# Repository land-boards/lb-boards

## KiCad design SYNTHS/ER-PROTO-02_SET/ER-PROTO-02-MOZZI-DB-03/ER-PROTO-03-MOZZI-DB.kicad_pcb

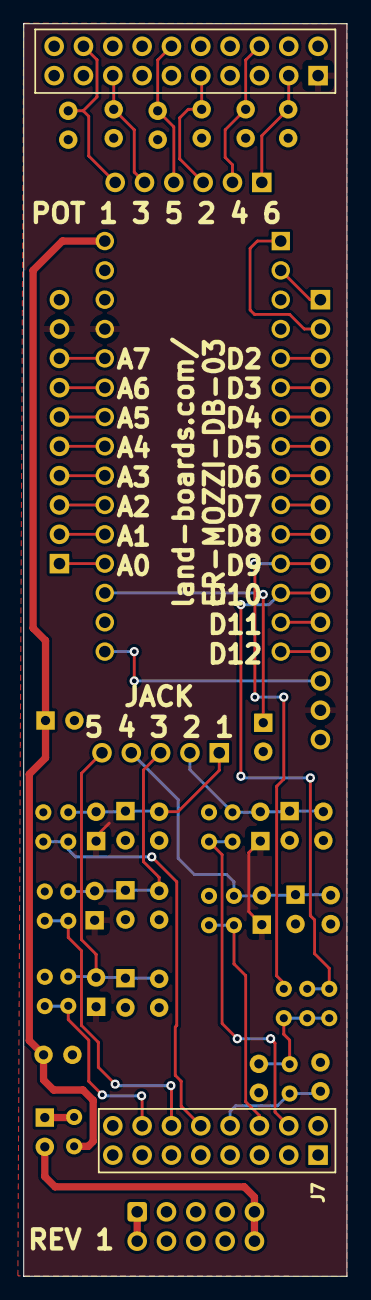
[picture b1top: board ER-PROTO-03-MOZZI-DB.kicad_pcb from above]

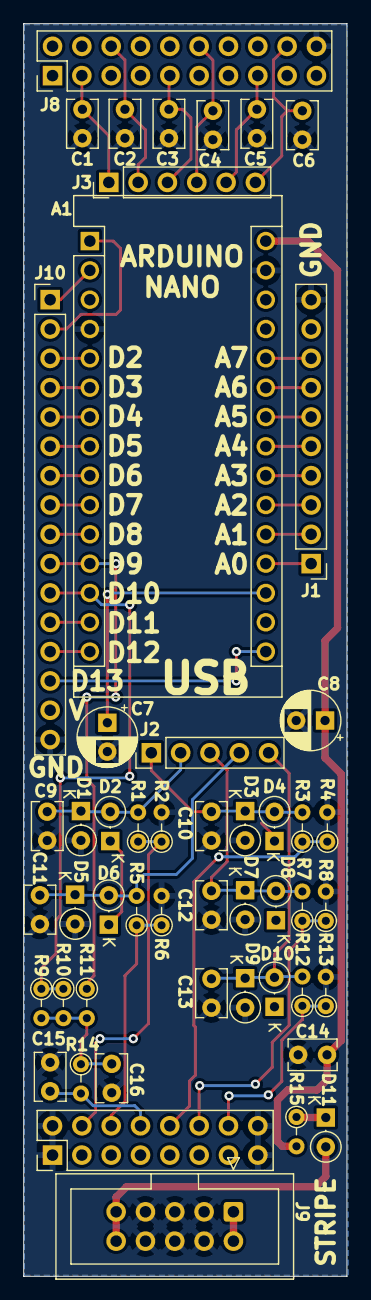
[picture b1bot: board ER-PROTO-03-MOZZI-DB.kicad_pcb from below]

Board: 2 copper layers, 28.0 x 108.5 mm, 50 parts (50 on the bottom side), 47 nets.

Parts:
A1: Arduino_Nano_v3.x; Arduino_Nano
C1, C2, C3, C4, C5, C6, C9, C10, C11, C12, C13, C14: 0.1uF; C_Rect_L4.0mm_W2.5mm_P2.50mm
C7: 10uF; CP_Radial_D5.0mm_P2.50mm
C8: 47uF; CP_Radial_D5.0mm_P2.50mm
C15: 10nF; C_Rect_L4.0mm_W2.5mm_P2.50mm
C16: 4.7nF; C_Rect_L4.0mm_W2.5mm_P2.50mm
D1, D2, D3, D4, D5, D6, D7, D8, D9, D10, D11: BAT41; D_DO-35_SOD27_P2.54mm_Vertical_KathodeUp
J1: Conn_01x10; PinHeader_1x10_P2.54mm_Vertical
J2: Conn_01x05; PinHeader_1x05_P2.54mm_Vertical
J3: Conn_01x06; PinHeader_1x06_P2.54mm_Vertical
J7: PROTO02_JACKS; PinHeader_2x08_P2.54mm_Vertical
J8: PROTO02_POTS; PinHeader_2x10_P2.54mm_Vertical
J9: CONN, IDC, 2X5; IDC-Header_2x05_P2.54mm_Vertical
J10: Conn_01x16; PinHeader_1x16_P2.54mm_Vertical
R1, R3, R5, R7, R12: 10K; R_Axial_DIN0204_L3.6mm_D1.6mm_P2.54mm_Vertical
R2, R4, R6, R8, R13: 100K; R_Axial_DIN0204_L3.6mm_D1.6mm_P2.54mm_Vertical
R9, R10: 1M; R_Axial_DIN0204_L3.6mm_D1.6mm_P2.54mm_Vertical
R11, R14: 3.9K; R_Axial_DIN0204_L3.6mm_D1.6mm_P2.54mm_Vertical
R15: 10; R_Axial_DIN0204_L3.6mm_D1.6mm_P2.54mm_Vertical

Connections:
+5V: A1.27 (+5V), D2.1 (K), D4.1 (K), D6.1 (K), D8.1 (K), D10.1 (K), J1.9, J8.1 (VCC), J10.15
+12P: A1.30 (VIN), C8.1, C14.1, R15.2
+12V: D11.2 (A), J9.9, J9.10
-12V: J9.1, J9.2
/ANA0: A1.19 (A0), J1.1
/ANA1: A1.20 (A1), J1.2
/ANA2: A1.21 (A2), J1.3
/ANA3: A1.22 (A3), J1.4
/ANA4: A1.23 (A4), J1.5
/ANA5: A1.24 (A5), J1.6
/ANA6: A1.25 (A6), J1.7
/ANA7: A1.26 (A7), J1.8
/D0_RX: A1.2 (D0/RX), J10.1
/D1_TX: A1.1 (D1/TX), J10.2
/D2: A1.5 (D2), J10.3
/D3: A1.6 (D3), J10.4
/D4: A1.7 (D4), J10.5
/D5: A1.8 (D5), J10.6
/D6: A1.9 (D6), J10.7
/D7: A1.10 (D7), J10.8
/D8: A1.11 (D8), J10.9
/D9: A1.12 (D9), J10.10, R11.1
/D10: A1.13 (D10), J10.11, R9.1, R10.1
/D11: A1.14 (D11), J10.12
/D12: A1.15 (D12), J10.13
/D13: A1.16 (D13), J10.14
/J1-T: J7.10 (J1_T), R3.1, R4.1
/J1-TIP: C10.1, D3.1 (K), D4.2 (A), J2.1, R3.2
/J2-T: J7.4 (J2_T), R1.1, R2.1
/J2-TIP: C9.1, D1.1 (K), D2.2 (A), J2.2, R1.2
/J3-T: J7.12 (J3_T), R7.1, R8.1
/J3-TIP: C12.1, D7.1 (K), D8.2 (A), J2.3, R7.2
/J4-T: J7.6 (J4_T), R5.1, R6.1
/J4-TIP: C11.1, D5.1 (K), D6.2 (A), J2.4, R5.2
/J5-T: J7.14 (J5_T), R12.1, R13.1
/J5-TIP: C13.1, D9.1 (K), D10.2 (A), J2.5, R12.2
/J6-T: C15.1, J7.8 (J6_T), R14.2
/POT1-2: C6.1, J3.6, J8.18 (POT1_2_W)
/POT2-2: C3.1, J3.3, J8.9 (POT2_2_W)
/POT3-2: C5.1, J3.5, J8.15 (POT3_2_W)
/POT4-2: C2.1, J3.2, J8.6 (POT4_2_W)
/POT5-2: C4.1, J3.4, J8.12 (POT5_2_W)
/POT6-2: C1.1, J3.1, J8.3 (POT6_2_W)
GND: A1.4 (GND), A1.29 (GND), C1.2, C2.2, C3.2, C4.2, C5.2, C6.2, C7.2, C8.2, C9.2, C10.2, C11.2, C12.2, C13.2, C14.2, C15.2, C16.2, D1.2 (A), D3.2 (A), D5.2 (A), D7.2 (A), D9.2 (A), J1.10, J7.1 (GND), J7.2 (GND), J7.15 (GND), J7.16 (GND), J8.20 (GND), J9.3, J9.4, J9.5, J9.6, J9.7, J9.8, J10.16, R2.2, R4.2, R6.2, R8.2, R13.2
unnamed: A1.18 (AREF), C7.1
unnamed: C16.1, R9.2, R10.2, R11.2, R14.1
unnamed: D11.1 (K), R15.1

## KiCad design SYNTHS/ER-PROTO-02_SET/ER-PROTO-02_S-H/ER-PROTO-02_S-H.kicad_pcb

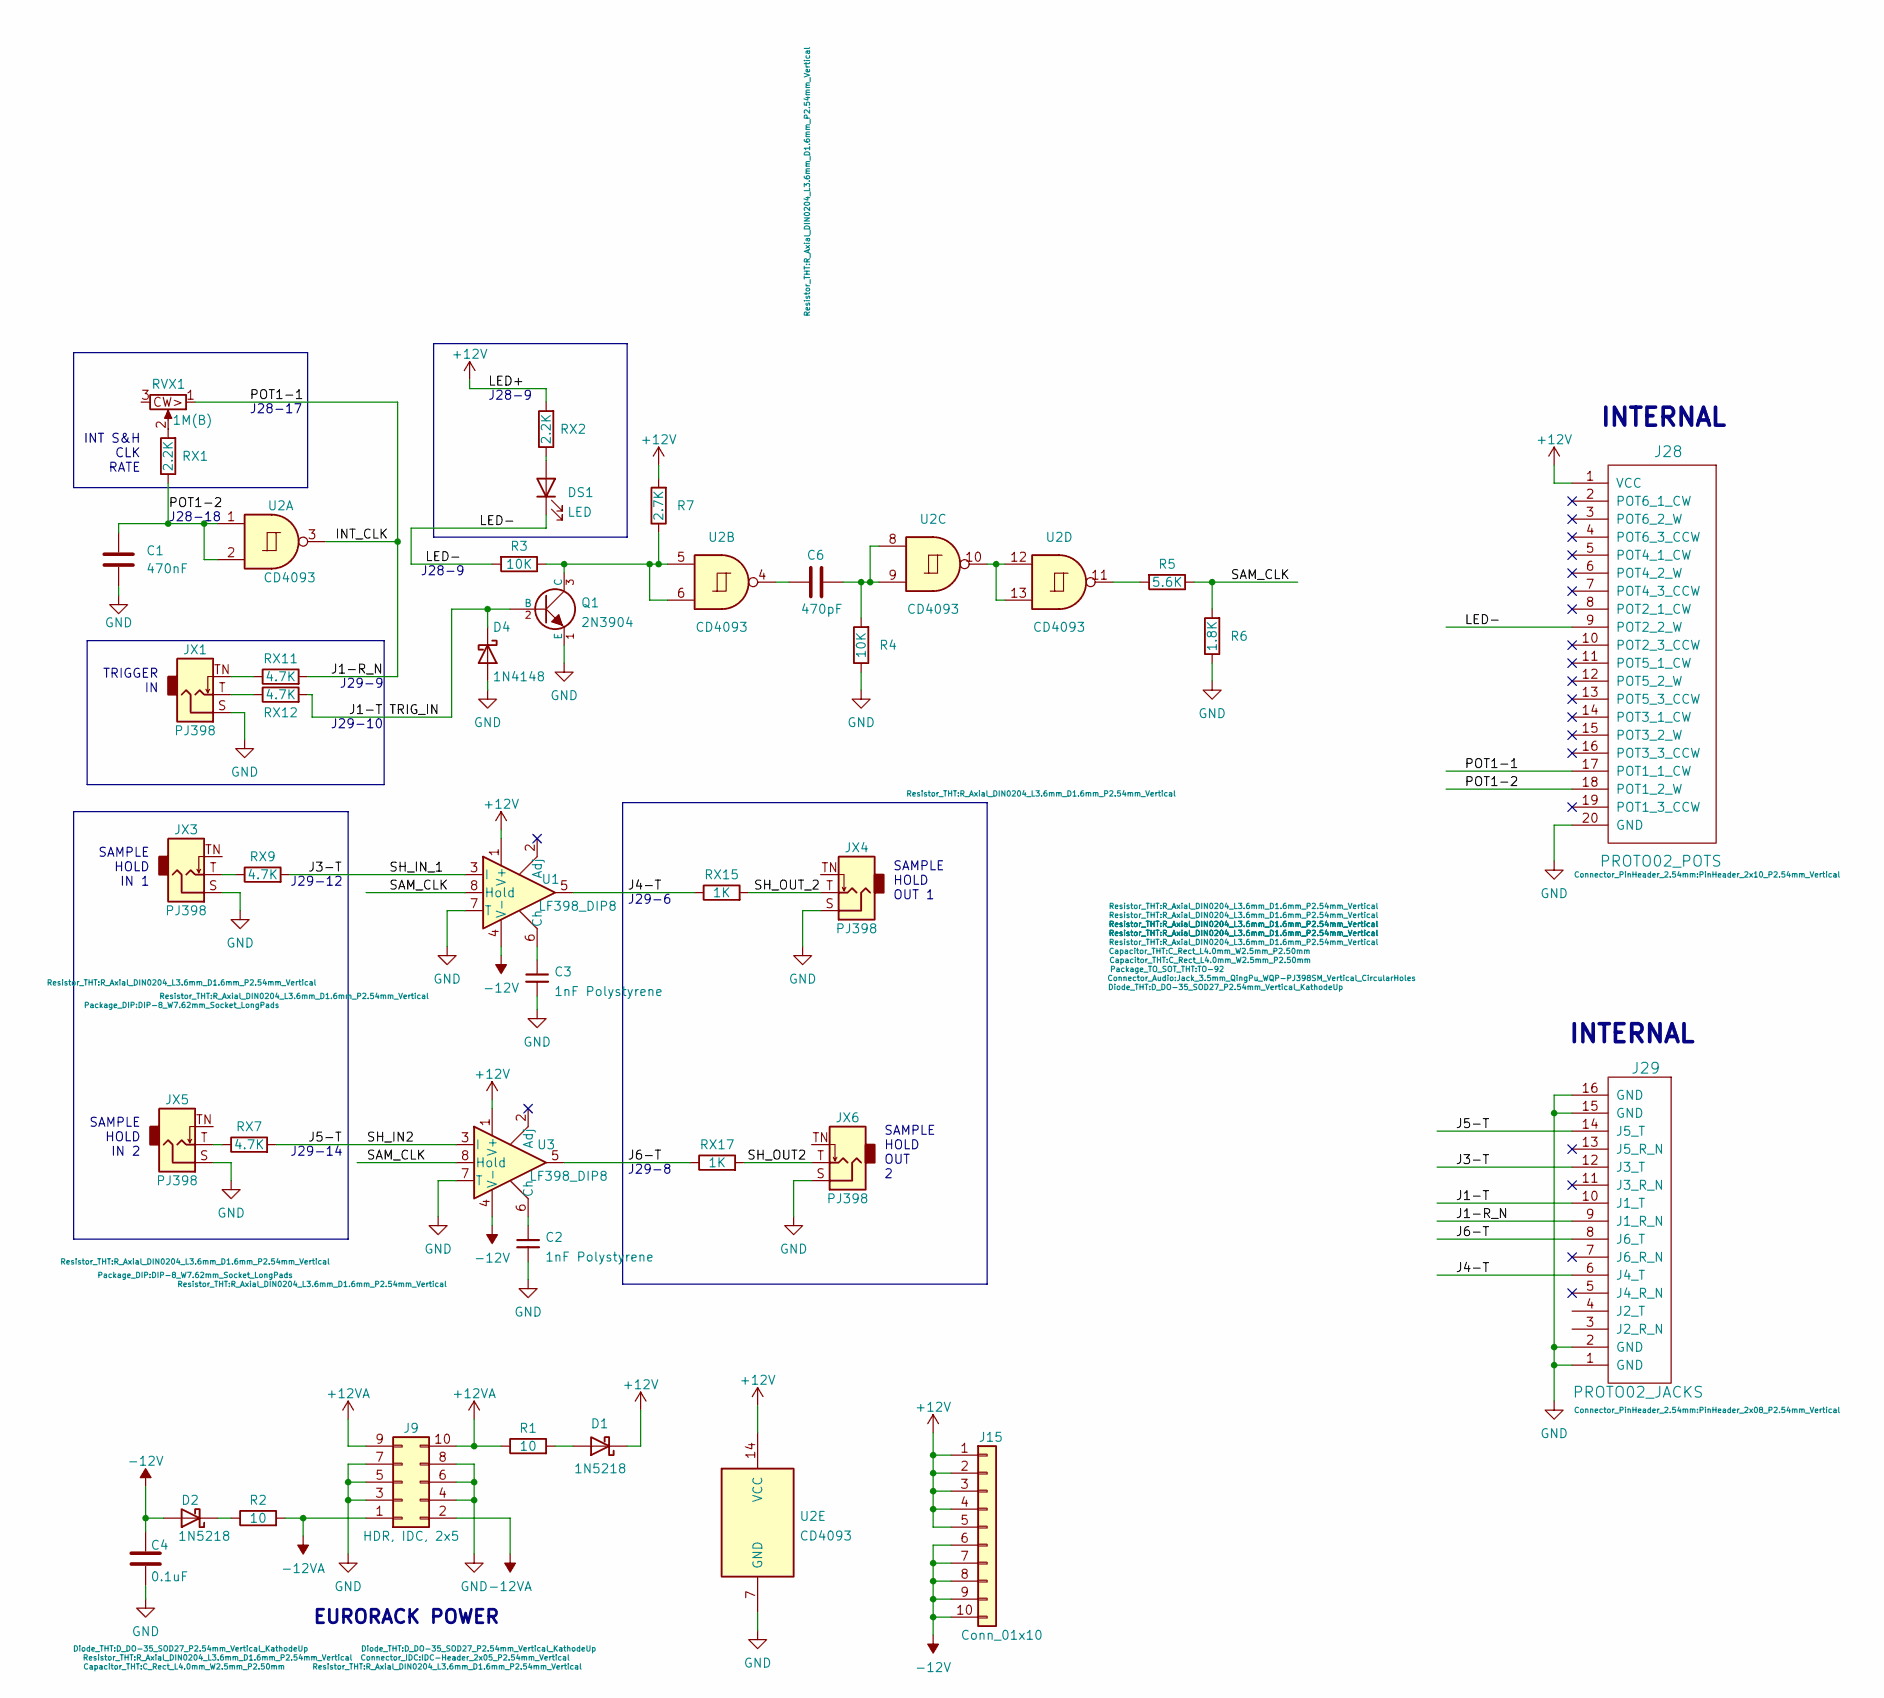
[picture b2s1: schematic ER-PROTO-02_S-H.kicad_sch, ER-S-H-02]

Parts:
C1: 470nF; C_Rect_L4.0mm_W2.5mm_P2.50mm
C2, C3: 1nF Polystyrene; C_Radial_D5.0mm_H7.0mm_P2.00mm
C4: 0.1uF; C_Rect_L4.0mm_W2.5mm_P2.50mm
C6: 470pF; C_Rect_L4.0mm_W2.5mm_P2.50mm
D1, D2: 1N5218; D_DO-35_SOD27_P2.54mm_Vertical_KathodeUp
D4: 1N4148; D_DO-35_SOD27_P2.54mm_Vertical_KathodeUp
DS1: LED; LED_D5.0mm
J9: HDR, IDC, 2x5; IDC-Header_2x05_P2.54mm_Vertical
J15: Conn_01x10; PinHeader_1x10_P2.54mm_Vertical
J28: PROTO02_POTS; PinHeader_2x10_P2.54mm_Vertical
J29: PROTO02_JACKS; PinHeader_2x08_P2.54mm_Vertical
JX1, JX3, JX4, JX5, JX6: PJ398; Jack_3.5mm_QingPu_WQP-PJ398SM_Vertical_CircularHoles
Q1: 2N3904; TO-92
R1, R2: 10; R_Axial_DIN0204_L3.6mm_D1.6mm_P2.54mm_Vertical
R3, R4: 10K; R_Axial_DIN0204_L3.6mm_D1.6mm_P2.54mm_Vertical
R5: 5.6K; R_Axial_DIN0204_L3.6mm_D1.6mm_P2.54mm_Vertical
R6: 1.8K; R_Axial_DIN0204_L3.6mm_D1.6mm_P2.54mm_Vertical
R7: 2.7K; R_Axial_DIN0204_L3.6mm_D1.6mm_P2.54mm_Vertical
RVX1: 1M(B); RV09ACF
RX1, RX2: 2.2K; R_Axial_DIN0204_L3.6mm_D1.6mm_P2.54mm_Vertical
RX7, RX9, RX11, RX12: 4.7K; R_Axial_DIN0204_L3.6mm_D1.6mm_P2.54mm_Vertical
RX15, RX17: 1K; R_Axial_DIN0204_L3.6mm_D1.6mm_P2.54mm_Vertical
U1, U3: LF398_DIP8; DIP-8_W7.62mm_Socket_LongPads
U2: CD4093; DIP-14_W7.62mm_Socket_LongPads

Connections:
+12V: D1.1 (K), J15.1, J15.2, J15.3, J15.4, J15.5, J28.1 (VCC), R7.2, RX2.2, U1.1 (V+), U2.14 (VCC), U3.1 (V+)
+12VA: J9.9, J9.10, R1.1
-12V: C4.1, D2.2 (A), J15.6, J15.7, J15.8, J15.9, J15.10, U1.4 (V-), U3.4 (V-)
-12VA: J9.1, J9.2, R2.2
/INT_CLK: J28.17 (POT1_1_CW), J29.9 (J1_R_N), RVX1.1, RX11.2, U2.3
/J1-T: D4.1 (K), J29.10 (J1_T), Q1.2 (B), RX12.2
/J3-T: J29.12 (J3_T), RX9.2, U1.3 (I)
/J4-T: J29.6 (J4_T), RX15.1, U1.5
/J5-T: J29.14 (J5_T), RX7.2, U3.3 (I)
/J6-T: J29.8 (J6_T), RX17.1, U3.5
/LED-: DS1.1 (K), J28.9 (POT2_2_W), R3.2
/POT1-2: C1.1, J28.18 (POT1_2_W), RX1.1, U2.1, U2.2
/SAM_CLK: R5.1, R6.2, U1.8 (Hold), U3.8 (Hold)
/SH_OUT2: JX6.T, RX17.2
/SH_OUT_2: JX4.T, RX15.2
GND: C1.2, C2.2, C3.2, C4.2, D4.2 (A), J9.3, J9.4, J9.5, J9.6, J9.7, J9.8, J28.20 (GND), J29.1 (GND), J29.2 (GND), J29.15 (GND), J29.16 (GND), JX1.S, JX3.S, JX4.S, JX5.S, JX6.S, Q1.1 (E), R4.1, R6.1, U1.7 (T), U2.7 (GND), U3.7 (T)
unnamed: C2.1, U3.6 (Ch)
unnamed: C3.1, U1.6 (Ch)
unnamed: C6.1, U2.4
unnamed: C6.2, R4.2, U2.8, U2.9
unnamed: D1.2 (A), R1.2
unnamed: D2.1 (K), R2.1
unnamed: DS1.2 (A), RX2.1
unnamed: JX1.T, RX12.1
unnamed: JX1.TN, RX11.1
unnamed: JX3.T, RX9.1
unnamed: JX5.T, RX7.1
unnamed: Q1.3 (C), R3.1, R7.1, U2.5, U2.6
unnamed: R5.2, U2.11
unnamed: RVX1.2, RX1.2
unnamed: U2.10, U2.12, U2.13

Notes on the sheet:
SAMPLE HOLD OUT 2
EURORACK POWER
INT S&H CLK RATE
J29-8
SAMPLE HOLD OUT 1
J29-14
J28-17
J29-6
SAMPLE HOLD IN 2
J28-9
TRIGGER IN
J28-18
J29-12
SAMPLE HOLD IN 1
J29-9
INTERNAL
J29-10

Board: 2 copper layers, 38 parts (0 on the bottom side), 31 nets, no tracks yet.

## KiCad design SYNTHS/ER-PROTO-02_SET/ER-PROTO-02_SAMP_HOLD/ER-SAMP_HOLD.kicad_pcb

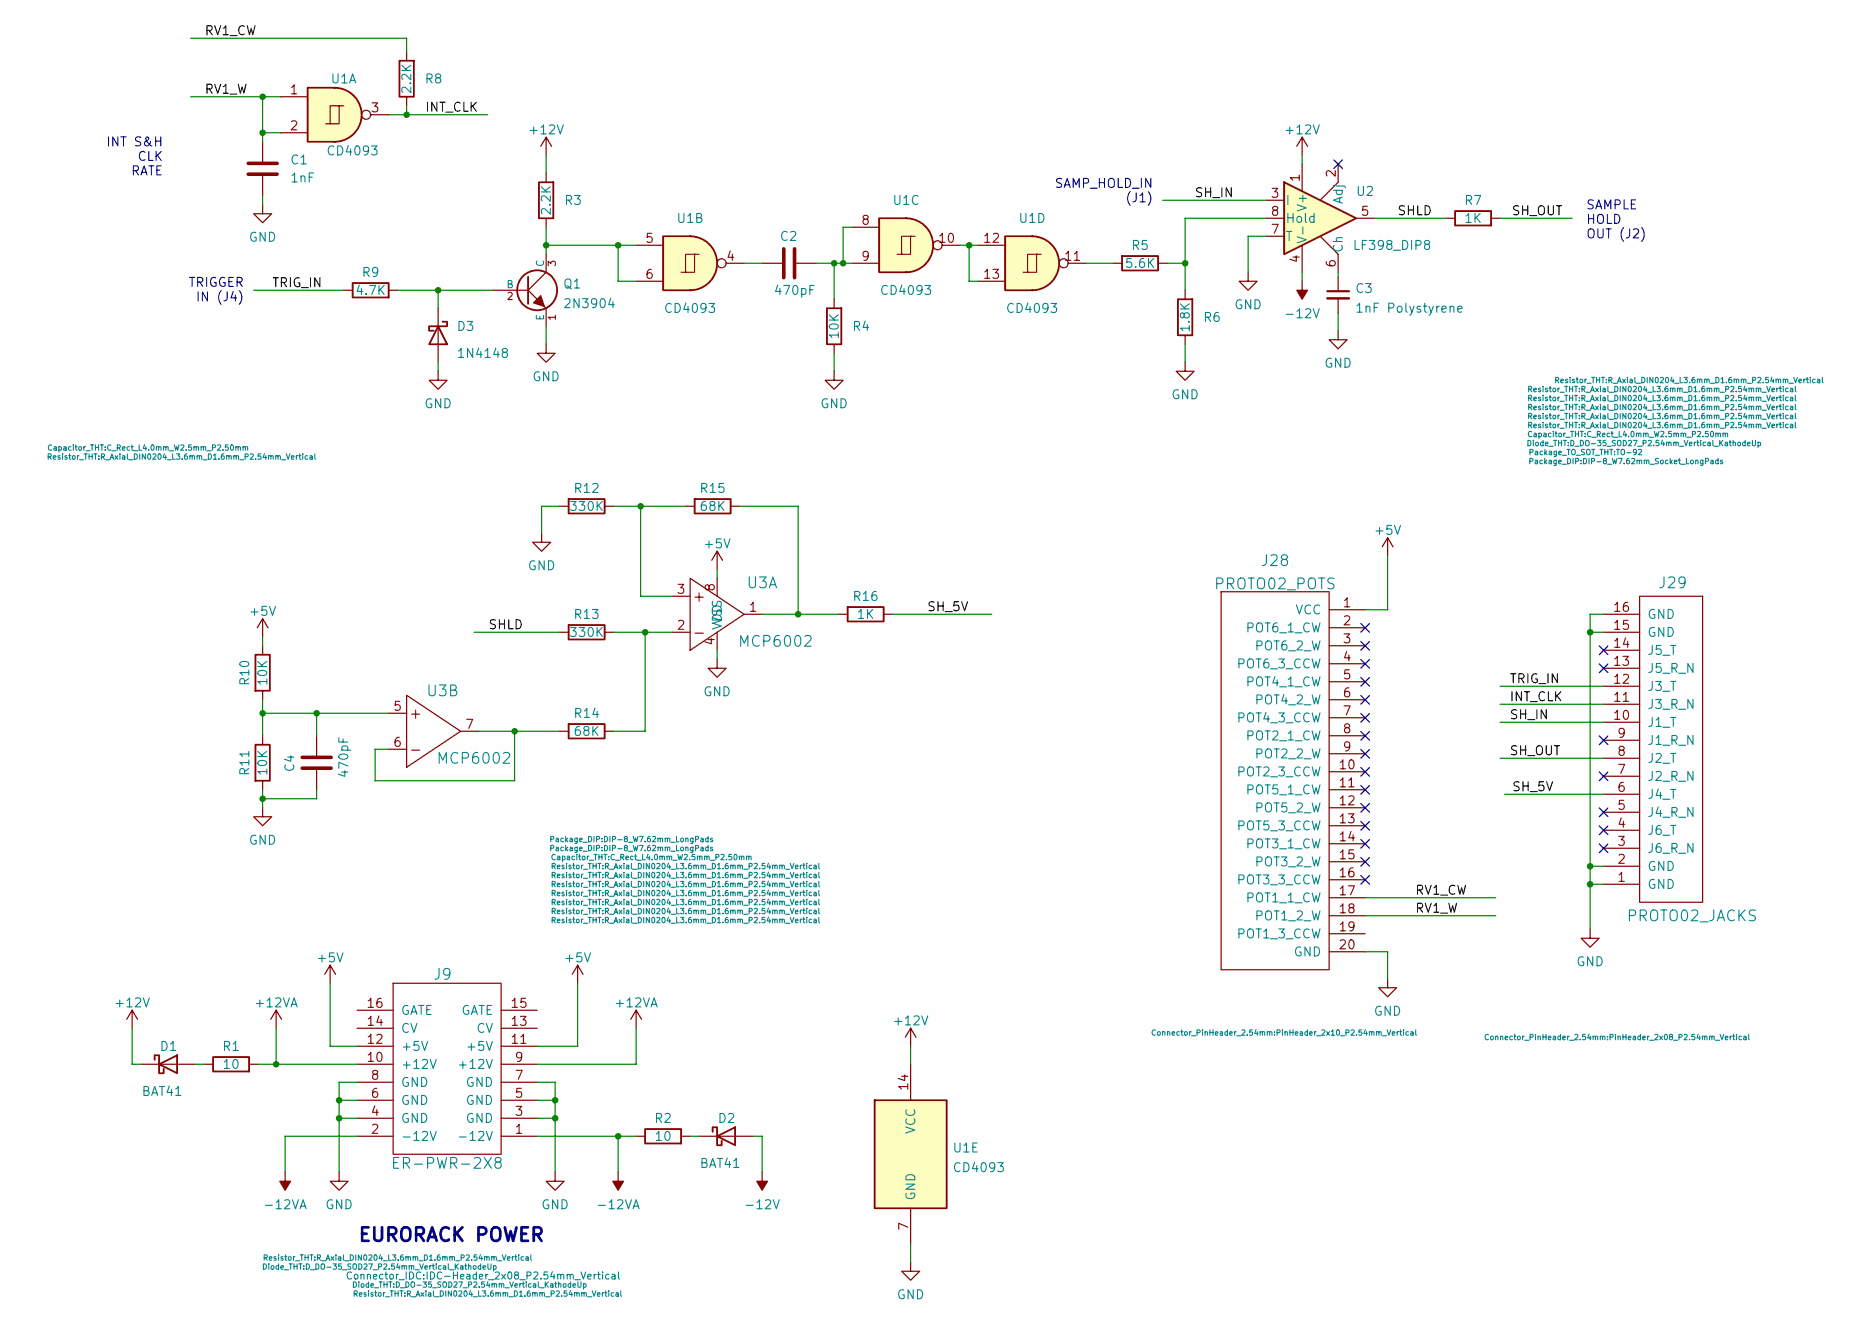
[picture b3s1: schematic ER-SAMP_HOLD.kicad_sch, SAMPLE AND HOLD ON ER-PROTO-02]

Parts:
C1: 1nF; C_Rect_L4.0mm_W2.5mm_P2.50mm
C2, C4: 470pF; C_Rect_L4.0mm_W2.5mm_P2.50mm
C3: 1nF Polystyrene; C_Radial_D5.0mm_H7.0mm_P2.00mm
D1, D2: BAT41; D_DO-35_SOD27_P2.54mm_Vertical_KathodeUp
D3: 1N4148; D_DO-35_SOD27_P2.54mm_Vertical_KathodeUp
J9: ER-PWR-2X8; IDC-Header_2x08_P2.54mm_Vertical
J28: PROTO02_POTS; PinHeader_2x10_P2.54mm_Vertical
J29: PROTO02_JACKS; PinHeader_2x08_P2.54mm_Vertical
Q1: 2N3904; TO-92
R1, R2: 10; R_Axial_DIN0204_L3.6mm_D1.6mm_P2.54mm_Vertical
R3, R8: 2.2K; R_Axial_DIN0204_L3.6mm_D1.6mm_P2.54mm_Vertical
R4, R10, R11: 10K; R_Axial_DIN0204_L3.6mm_D1.6mm_P2.54mm_Vertical
R5: 5.6K; R_Axial_DIN0204_L3.6mm_D1.6mm_P2.54mm_Vertical
R6: 1.8K; R_Axial_DIN0204_L3.6mm_D1.6mm_P2.54mm_Vertical
R7, R16: 1K; R_Axial_DIN0204_L3.6mm_D1.6mm_P2.54mm_Vertical
R9: 4.7K; R_Axial_DIN0204_L3.6mm_D1.6mm_P2.54mm_Vertical
R12, R13: 330K; R_Axial_DIN0204_L3.6mm_D1.6mm_P2.54mm_Vertical
R14, R15: 68K; R_Axial_DIN0204_L3.6mm_D1.6mm_P2.54mm_Vertical
U1: CD4093; DIP-14_W7.62mm_Socket_LongPads
U2: LF398_DIP8; DIP-8_W7.62mm_Socket_LongPads
U3: MCP6002; DIP-8_W7.62mm_LongPads

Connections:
+5V: J9.11 (+5V), J9.12 (+5V), J28.1 (VCC), R10.1, U3.8 (VDD)
+12V: D1.1 (K), R3.2, U1.14 (VCC), U2.1 (V+)
+12VA: J9.9 (+12V), J9.10 (+12V), R1.2
-12V: D2.2 (A), U2.4 (V-)
-12VA: J9.1 (-12V), J9.2 (-12V), R2.1
/INT_CLK: J29.11 (J3_R_N), R8.1, U1.3
/RV1_CW: J28.17 (POT1_1_CW), R8.2
/RV1_W: C1.1, J28.18 (POT1_2_W), U1.1, U1.2
/SHLD: R7.1, R13.2, U2.5
/SH_5V: J29.6 (J4_T), R16.1
/SH_IN: J29.10 (J1_T), U2.3 (I)
/SH_OUT: J29.8 (J2_T), R7.2
/TRIG_IN: J29.12 (J3_T), R9.1
GND: C1.2, C3.2, C4.1, D3.2 (A), J9.3 (GND), J9.4 (GND), J9.5 (GND), J9.6 (GND), J9.7 (GND), J9.8 (GND), J28.20 (GND), J29.1 (GND), J29.2 (GND), J29.15 (GND), J29.16 (GND), Q1.1 (E), R4.1, R6.1, R11.2, R12.2, U1.7 (GND), U2.7 (T), U3.4 (VSS)
unnamed: C2.1, U1.4
unnamed: C2.2, R4.2, U1.8, U1.9
unnamed: C3.1, U2.6 (Ch)
unnamed: D1.2 (A), R1.1
unnamed: D2.1 (K), R2.2
unnamed: D3.1 (K), Q1.2 (B), R9.2
unnamed: Q1.3 (C), R3.1, U1.5, U1.6
unnamed: R5.1, R6.2, U2.8 (Hold)
unnamed: R5.2, U1.11
unnamed: U1.10, U1.12, U1.13
unnamed: R15.1, R16.2, U3.1 (Q)
unnamed: R13.1, R14.1, U3.2 (-)
unnamed: R12.1, R15.2, U3.3 (+)
unnamed: C4.2, R10.2, R11.1, U3.5 (+)
unnamed: R14.2, U3.6 (-), U3.7 (Q)

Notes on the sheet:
SAMPLE HOLD OUT (J2)
SAMP_HOLD_IN (J1)
EURORACK POWER
INT S&H CLK RATE
TRIGGER IN (J4)

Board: 2 copper layers, 30 parts (2 on the bottom side), 29 nets, no tracks yet.
